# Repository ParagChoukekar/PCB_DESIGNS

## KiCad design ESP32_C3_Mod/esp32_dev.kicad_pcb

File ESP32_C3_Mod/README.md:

## PCB Design Details
## Overview

This project is an educational recreation of an **ESP32-C3 module** designed
in **KiCad** using publicly available **Espressif** reference schematics,
hardware design guidelines, and PCB layout recommendations.

The purpose of this project is to study and better understand:
- ESP32-C3 hardware design
- PCB layout and routing practices
- Power regulation design
- RF design considerations

This project was created solely for educational and learning purposes.
It is not an official Espressif design, product, or reference module.
All design references and technical resources belong to their respective owners.

## Antenna Design

The PCB antenna footprint used in this project was referenced from the
official KiCad RF antenna footprint library:

- [KiCad RF Antenna Footprints](https://kicad.github.io/footprints/RF_Antenna.html)
- You can download the library [here.](https://kicad.github.io/download/footprints/RF_Antenna.pretty.7z)

A custom schematic symbol was created for the
`Texas_SWRA117D_2.4GHz_Left` PCB antenna to integrate it into the
ESP32-C3 schematic and PCB design workflow.
> Note: RF performance and antenna tuning were not professionally validated.
This project is intended for educational and PCB design learning purposes only.
---
### 🔹 Top Layer

---

### 🔹 Bottom Layer

---

### 🔹 Gnd Layer

---

### 🔹 Signal Layer

---

### 🔹 All Layers

---

### 🔹 3D View

## Resources

The following official Espressif resources were used as references during
the design process:

- [Espressif Hardware Design Guidelines](https://docs.espressif.com/projects/esp-hardware-design-guidelines/en/latest/esp32c3/index.html)
- [ESP32-C3 Technical Reference Manual](https://documentation.espressif.com/esp32-c3_technical_reference_manual_en.pdf)
- [ESP32-C3-WROOM-02_Reference_Design](docs/ESP32-C3-WROOM-02_Reference_Design/)

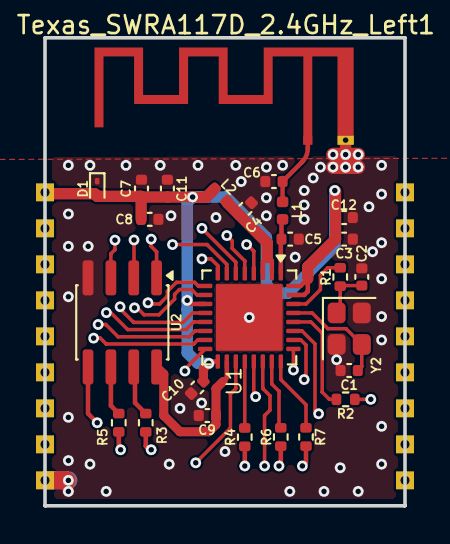
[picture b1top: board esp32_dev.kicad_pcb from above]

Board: 4 copper layers, 20.0 x 26.0 mm, 44 parts (0 on the bottom side), 37 nets.

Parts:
3V3: TestPoint_THTPad_1.0x1.0mm_Drill0.5mm
C1, C2, C3, C4, C5, C6, C7, C8, C9, C10, C11, C12: C; C_0402_1005Metric
D1: ESD9B3.3ST5G; D_SOD-923
EN: TestPoint_THTPad_1.0x1.0mm_Drill0.5mm
GND: TestPoint_THTPad_1.0x1.0mm_Drill0.5mm
IO0, IO1, IO2, IO3, IO4, IO5, IO6, IO7, IO8, IO9, IO10, IO18, IO19: TestPoint_THTPad_1.0x1.0mm_Drill0.5mm
L1, L2: L; L_0402_1005Metric
R1, R2, R3, R4, R5, R6, R7: R_US; R_0402_1005Metric
RXD0: TestPoint_THTPad_1.0x1.0mm_Drill0.5mm
TXD0: TestPoint_THTPad_1.0x1.0mm_Drill0.5mm
Texas_SWRA117D_2.4GHz_Left1: Texas_SWRA117D_2.4GHz_Left
U1: ESP32-C3; QFN-32-1EP_5x5mm_P0.5mm_EP3.7x3.7mm
U2: W25X40CLSN; SOIC-8_3.9x4.9mm_P1.27mm
Y2: Crystal_GND24; Crystal_SMD_2520-4Pin_2.5x2.0mm

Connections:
/CHIP_EN: EN.1 (Pin_1_1), U1.7 (CHIP_EN)
/GPIO0: IO0.1 (Pin_1_1), U1.4 (XTAL_32K_P)
/GPIO1: IO1.1 (Pin_1_1), U1.5 (XTAL_32K_N)
/GPIO2: IO2.1 (Pin_1_1), U1.6 (GPIO2)
/GPIO3: IO3.1 (Pin_1_1), U1.8 (GPIO3)
/GPIO4: IO4.1 (Pin_1_1), U1.9 (MTMS)
/GPIO5: IO5.1 (Pin_1_1), U1.10 (MTDI)
/GPIO6: IO6.1 (Pin_1_1), U1.12 (MTCK)
/GPIO7: IO7.1 (Pin_1_1), U1.13 (MTDO)
/GPIO8: IO8.1 (Pin_1_1), U1.14 (GPIO8)
/GPIO9: IO9.1 (Pin_1_1), U1.15 (GPIO9)
/GPIO10: IO10.1 (Pin_1_1), U1.16 (GPIO10)
/GPIO18: IO18.1 (Pin_1_1), U1.25 (GPIO18)
/GPIO19: IO19.1 (Pin_1_1), U1.26 (GPIO19)
/LNA_IN: C5.1, L1.1, U1.1 (LNA_IN)
/SPICLK: R5.2, U2.6 (CLK)
/SPICS0: U1.21 (SPICS0), U2.1 (~CS)
/SPID: R6.2, U2.5 (DI/IO_{0})
/SPIHD: R3.2, U2.7 (~HOLD)
/SPIQ: R7.2, U2.2 (DO/IO_{1})
/SPIWP: R4.2, U2.3 (~WP)
/U0RXD: RXD0.1 (Pin_1_1), U1.27 (U0RXD)
/U0TXD: R2.1, TXD0.1 (Pin_1_1)
/VDD33: 3V3.1 (Pin_1_1), C3.1, C7.1, C8.2, C10.1, C11.1, C12.1, D1.2 (A2), L2.1, U1.11 (VDD3P3_RTC), U1.17 (VDD3P3_CPU), U1.31 (VDDA), U1.32 (VDDA)
/VDD_SPI: C9.2, U1.18 (VDD_SPI), U2.8 (VCC)
GND: C1.2, C2.2, C3.2, C4.2, C5.2, C6.2, C7.2, C8.1, C9.1, C10.2, C11.2, C12.2, D1.1 (A1), GND.1 (Pin_1_1), Texas_SWRA117D_2.4GHz_Left1.2 (GND), U1.33 (GND), U2.4 (GND), Y2.2 (G), Y2.4 (G)
unnamed: C2.1, R1.1, Y2.1
unnamed: C4.1, L2.2, U1.2 (VDD3P3), U1.3 (VDD3P3)
unnamed: C6.1, L1.2, Texas_SWRA117D_2.4GHz_Left1.1 (LNA_IN)
unnamed: R5.1, U1.22 (SPICLK)
unnamed: R6.1, U1.23 (SPID)
unnamed: R3.1, U1.19 (SPIHD)
unnamed: R7.1, U1.24 (SPIQ)
unnamed: R4.1, U1.20 (SPIWP)
unnamed: R2.2, U1.28 (U0TXD)
unnamed: C1.1, U1.29 (XTAL_N), Y2.3
unnamed: R1.2, U1.30 (XTAL_P)

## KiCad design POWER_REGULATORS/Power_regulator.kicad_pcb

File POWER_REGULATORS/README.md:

# Power Regulator

## Overview

This is an experimental PCB design focused on power regulation, converting
a **24V DC** input to regulated **5V** and **3.3V** outputs while keeping the
**bill of materials (BOM) minimal**.

### 3D VIEW

### Front Layout

### Front Layout

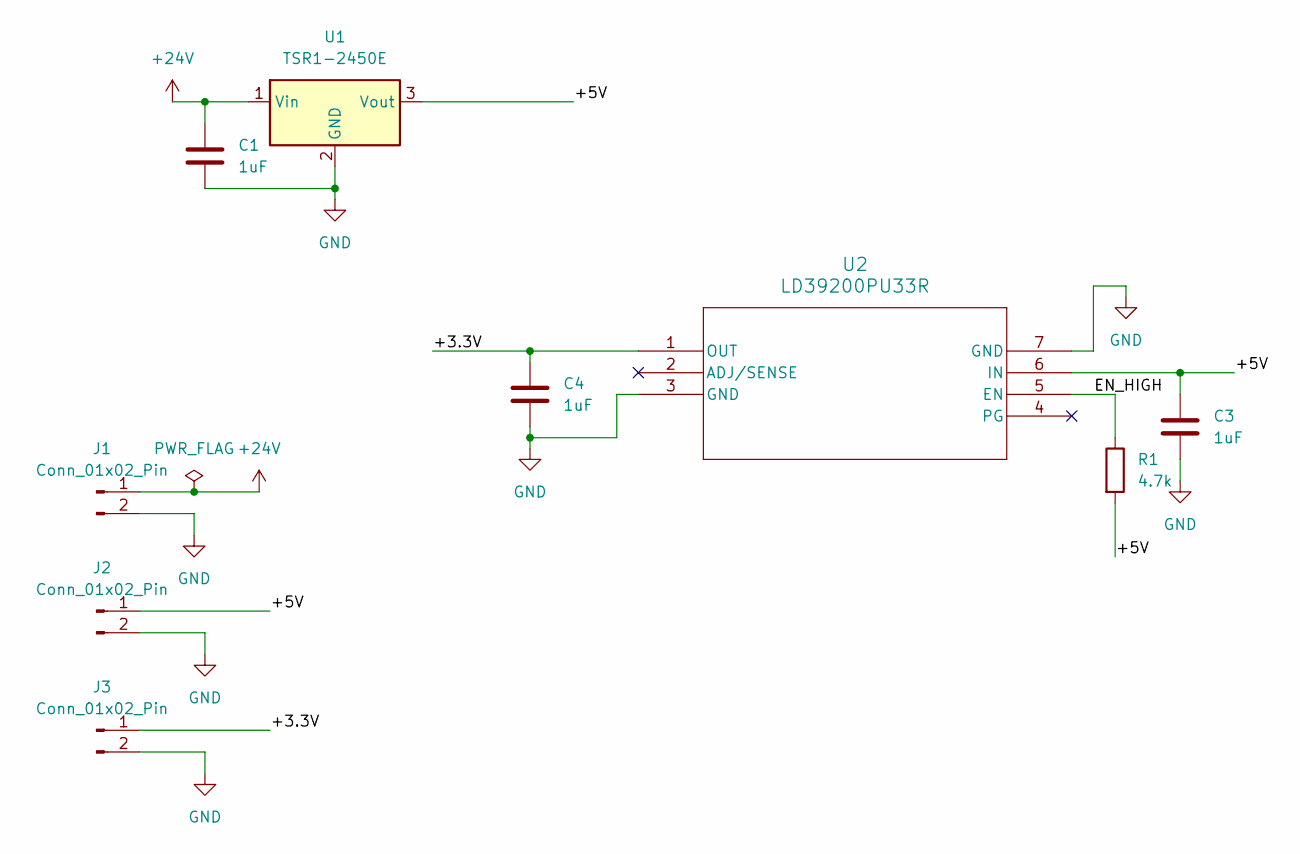
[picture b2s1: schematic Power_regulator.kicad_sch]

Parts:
C1, C3, C4: 1uF; C_0603_1608Metric
J1, J2, J3: Conn_01x02_Pin; PinHeader_1x02_P2.54mm_Vertical
R1: 4.7k; R_0603_1608Metric
U1: TSR1-2450E; Converter_DCDC_TRACO_TSR1-xxxxE_THT
U2: LD39200PU33R; SON_DFN6_3X3_STM

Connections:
+24V: C1.1, J1.1, U1.1 (Vin)
/+3.3V: C4.1, J3.1, U2.1 (OUT)
/+5V: C3.1, J2.1, R1.2, U1.3 (Vout), U2.6 (IN)
/EN_HIGH: R1.1, U2.5 (EN)
GND: C1.2, C3.2, C4.2, J1.2, J2.2, J3.2, U1.2 (GND), U2.3 (GND), U2.7 (GND)

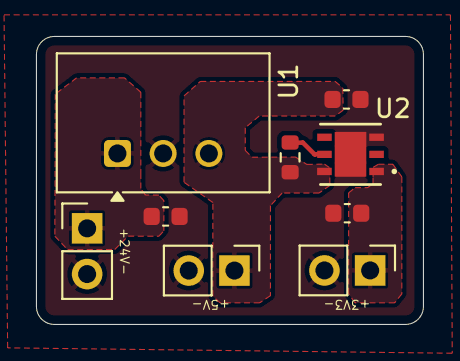
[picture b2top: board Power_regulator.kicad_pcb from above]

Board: 2 copper layers, 21.5 x 16.0 mm, 9 parts (0 on the bottom side), 5 nets.

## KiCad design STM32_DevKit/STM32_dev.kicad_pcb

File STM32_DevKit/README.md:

# STM32 DevKit 

## Overview
This repository contains a PCB design recreated in **KiCad** by following a
step-by-step tutorial from the **Phil’s Lab YouTube channel**.  
The project was made for learning and practice purposes.

## Credits
Original tutorial by **Phil’s Lab**  
YouTube Channel: [https://www.youtube.com/@PhilsLab](https://www.youtube.com/@PhilsLab)

### Front View

### Back View

### PCB Layout

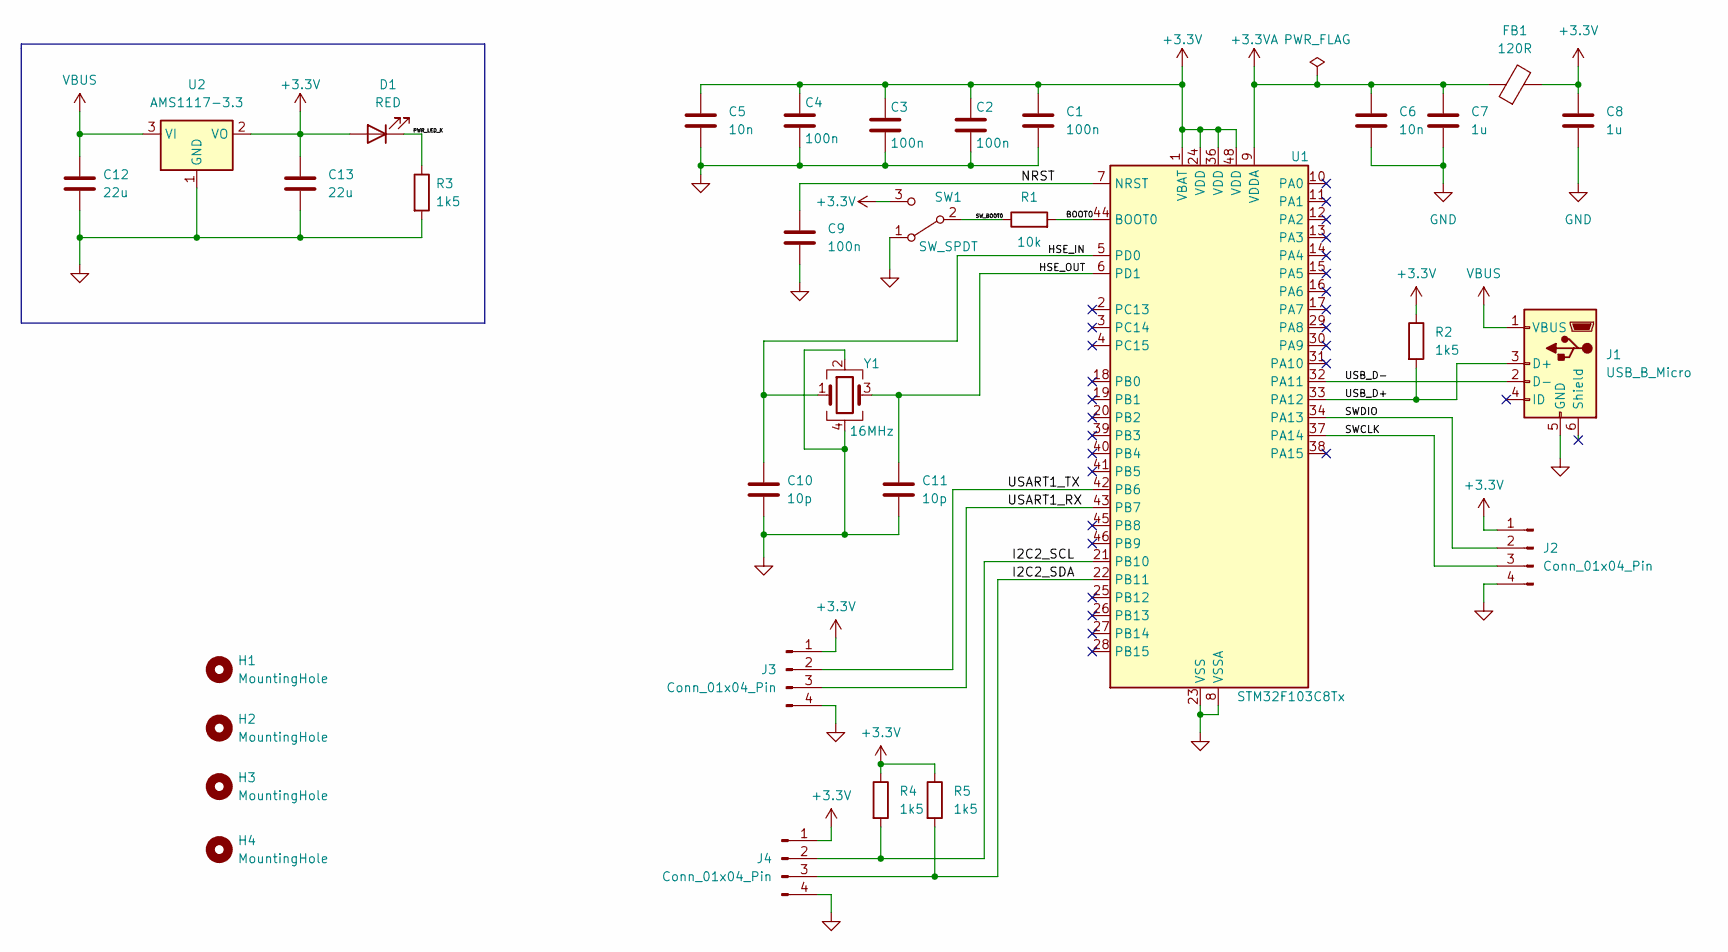
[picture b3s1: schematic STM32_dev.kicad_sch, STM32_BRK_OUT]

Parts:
C1, C2, C3, C4, C9: 100n; C_0402_1005Metric
C5: 10n; C_0603_1608Metric
C6: 10n; C_0402_1005Metric
C7, C8: 1u; C_0402_1005Metric
C10, C11: 10p; C_0402_1005Metric
C12, C13: 22u; C_0805_2012Metric
D1: RED; LED_0603_1608Metric
FB1: 120R; L_0603_1608Metric
H1, H2, H3, H4: MountingHole; MountingHole_2.2mm_M2
J1: USB_B_Micro; USB_Micro-B_Wuerth_629105150521
J2, J3, J4: Conn_01x04_Pin; PinHeader_1x04_P2.54mm_Vertical
R1: 10k; R_0402_1005Metric
R2, R3, R4, R5: 1k5; R_0402_1005Metric
SW1: SW_SPDT; SW_SPDT_PCM12
U1: STM32F103C8Tx; LQFP-48_7x7mm_P0.5mm
U2: AMS1117-3.3; SOT-223-3_TabPin2
Y1: 16MHz; Crystal_SMD_3225-4Pin_3.2x2.5mm

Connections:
+3.3V: C1.1, C2.1, C3.1, C4.1, C5.1, C8.1, C13.1, D1.2 (A), FB1.2, J2.1, J3.1, J4.1, R2.1, R4.1, R5.1, SW1.3 (C), U1.1 (VBAT), U1.24 (VDD), U1.36 (VDD), U1.48 (VDD), U2.2 (VO)
+3.3VA: C6.1, C7.1, FB1.1, U1.9 (VDDA)
/BOOT0: R1.2, U1.44 (BOOT0)
/HSE_IN: C10.1, U1.5 (PD0), Y1.1
/HSE_OUT: C11.1, U1.6 (PD1), Y1.3
/I2C2_SCL: J4.2, R4.2, U1.21 (PB10)
/I2C2_SDA: J4.3, R5.2, U1.22 (PB11)
/NRST: C9.1, U1.7 (NRST)
/PWR_LED_K: D1.1 (K), R3.1
/SWCLK: J2.3, U1.37 (PA14)
/SWDIO: J2.2, U1.34 (PA13)
/SW_BOOT0: R1.1, SW1.2 (B)
/USART1_RX: J3.3, U1.43 (PB7)
/USART1_TX: J3.2, U1.42 (PB6)
/USB_D+: J1.3 (D+), R2.2, U1.33 (PA12)
/USB_D-: J1.2 (D-), U1.32 (PA11)
GND: C1.2, C2.2, C3.2, C4.2, C5.2, C6.2, C7.2, C8.2, C9.2, C10.2, C11.2, C12.2, C13.2, J1.5 (GND), J2.4, J3.4, J4.4, R3.2, SW1.1 (A), U1.8 (VSSA), U1.23 (VSS), U1.35 (VSS), U1.47 (VSS), U2.1 (GND), Y1.2, Y1.4
VBUS: C12.1, J1.1 (VBUS), U2.3 (VI)

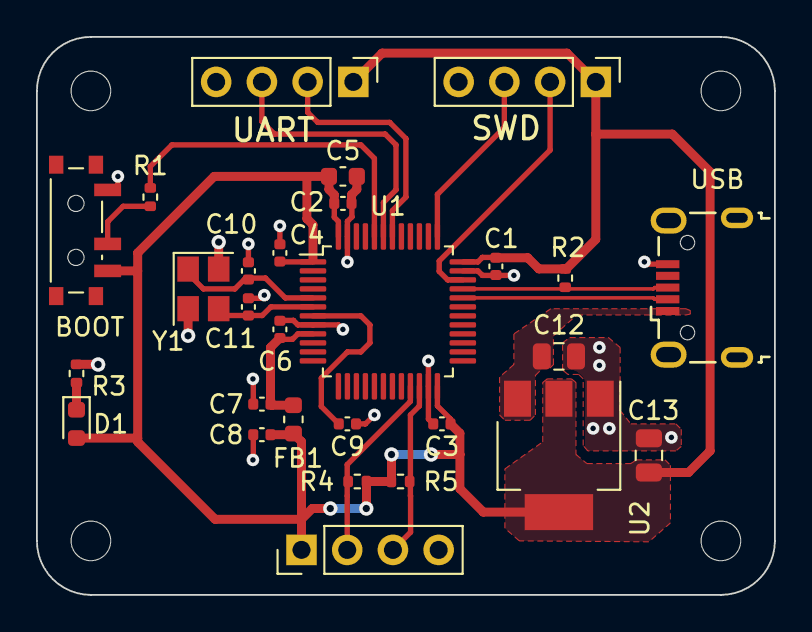
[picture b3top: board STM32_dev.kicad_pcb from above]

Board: 2 copper layers, 41.0 x 31.0 mm, 32 parts (0 on the bottom side), 18 nets.

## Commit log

2025-12-18 Create Images
2025-12-18 Update README with project details and images
    Added project overview and credits sections with images.
2025-12-18 Enhance README with project overview and images
    Added an overview and images for the power regulator PCB design.
2025-12-18 Add note about uploaded component datasheets
2026-05-04 Add README for ESP32_C3_Mod development documentation
2026-05-04 Add readme.txt for project images and layouts
2026-05-04 ADD "ESP32-C3-WROOM-02_Reference_Design" in docs
2026-05-04 ADD PCB Layout images via upload
2026-05-08 ADD 3D RENDERED IMAGES OF PCB DESIGNS
2026-05-08 Add PCB design details to README.md
2026-05-08 Enhance README with additional project details
    Expanded README with project overview, antenna design, and resources.
2026-05-08 ADD PROJECT FILES VIA UPLOAD
